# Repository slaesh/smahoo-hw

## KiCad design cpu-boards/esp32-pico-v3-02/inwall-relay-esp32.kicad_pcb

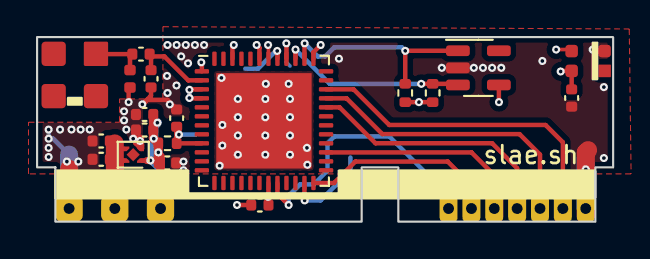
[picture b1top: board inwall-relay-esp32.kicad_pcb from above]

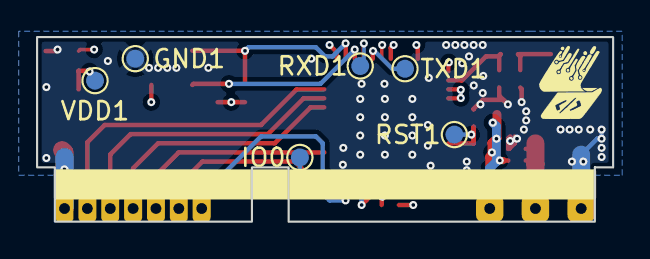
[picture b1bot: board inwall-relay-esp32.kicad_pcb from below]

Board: 4 copper layers, 32.0 x 10.3 mm, 26 parts (6 on the bottom side), 17 nets.

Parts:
C1, C2, C7: 1uF; C_0402_1005Metric
C3: 4.3nH; C_0402_1005Metric
C4: 0R; C_0402_1005Metric
C5: C; L_0402_1005Metric
C6, C8: 10uF; C_0402_1005Metric
C9, C10, C11: 100nF; C_0402_1005Metric
D1: WS2812B-2020; ws2812b-2020
GND1: TestPoint; TestPoint_Pad_D1.0mm
IO0: TestPoint; TestPoint_Pad_D1.0mm
J1: Conn_01x09_Male; inwall-relay-cpu
J2: ANTENNA; antenna_molex_479480001
R1, R2, R3: 10k; R_0402_1005Metric
RST1: TestPoint; TestPoint_Pad_D1.0mm
RXD1: TestPoint; TestPoint_Pad_D1.0mm
TXD1: TestPoint; TestPoint_Pad_D1.0mm
U1: ESP32-PICO-D4; QFN-48-1EP_7x7mm_P0.5mm_EP5.3x5.3mm
U2: NCP167; OnSemi_XDFN4-1EP_1.0x1.0mm_EP0.52x0.52mm
U3: 24AA02-OT; SOT-23-5
VDD1: TestPoint; TestPoint_Pad_D1.0mm

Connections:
BOARD_IO0: J1.4, U1.34 (IO5)
BOARD_IO1: J1.5, U1.33 (SD1)
BOARD_IO2: J1.6, U1.32 (SD0)
BOARD_IO4: J1.8, U1.24 (IO4)
BOARD_IO5: J1.9, U1.20 (IO13)
ESP_ANT: C3.1, C4.1, U1.2 (LNA_IN)
GND: C1.2, C2.2, C3.2, C5.1, C6.2, C7.2, C8.2, C9.2, C10.2, C11.2, D1.2 (VSS), GND1.1, J1.1, U1.49 (GND), U2.2 (GND), U3.2 (GND)
unnamed: C4.2, C5.2, J2.1
unnamed: C7.1, R1.2, RST1.1, U1.9 (EN)
unnamed: IO0.1, U1.23 (IO0)
unnamed: RXD1.1, U1.40 (U0RXD/IO3)
unnamed: TXD1.1, U1.41 (U0TXD/IO1)
SCL: R3.1, U1.38 (IO19), U3.1 (SCL)
SDA: R2.1, U1.39 (IO22), U3.3 (SDA)
VDD3V3: C2.1, C6.1, C9.1, C10.1, C11.1, D1.4 (VDD), J1.3, R1.1, R2.2, R3.2, U1.1 (VDDA), U1.3 (VDDA3P3), U1.4 (VDDA3P3), U1.19 (VDD3P3_RTC), U1.37 (VDD3P3_CPU), U1.43 (VDDA), U1.46 (VDDA), U2.1 (VOUT), U3.4 (VCC), VDD1.1
VIN: C1.1, C8.1, J1.2, U2.3 (/EN), U2.4 (VIN)
WS2812_DIN: D1.3 (DIN), U1.42 (IO21)

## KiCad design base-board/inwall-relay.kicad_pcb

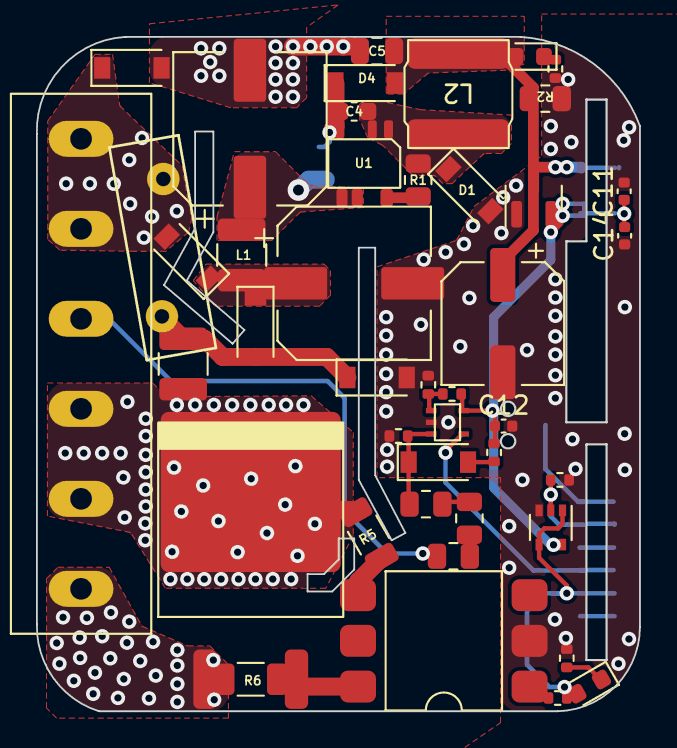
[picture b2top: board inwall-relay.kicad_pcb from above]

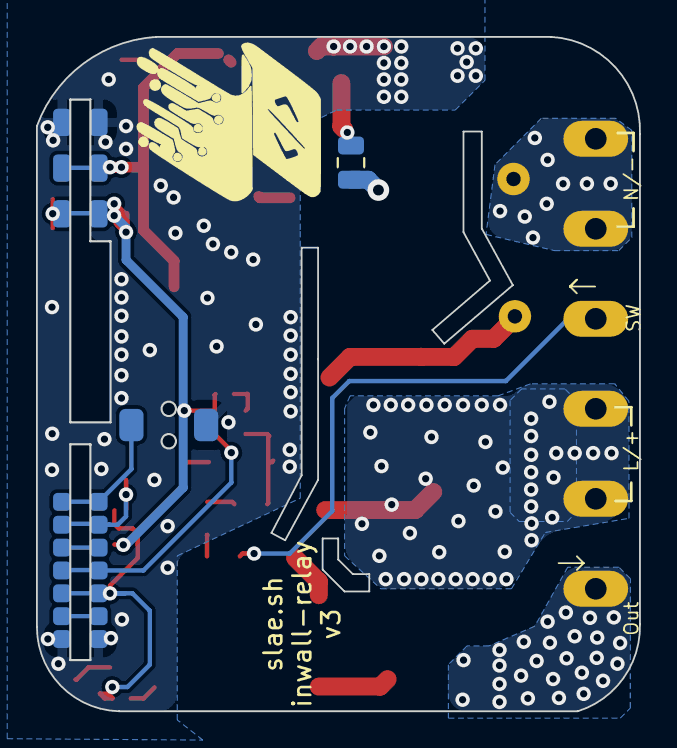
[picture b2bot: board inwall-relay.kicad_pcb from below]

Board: 2 copper layers, 33.5 x 37.5 mm, 46 parts (2 on the bottom side), 27 nets.

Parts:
C1, C3: 3.3uF; CP_Elec_8x10
C4: 1uF/16V; C_0603_1608Metric
C5: 22uF; C_0805_2012Metric
C8: 470uF; CP_Elec_6.3x7.7
C9: optional: 10pF / 500V; C_0805_2012Metric
C11: 22uF; C_0402_1005Metric
C12, C14: 100n; C_0402_1005Metric
D1: BAS21GWX; D_SOD-123
D2, D3, D4, D6, D7, D8: 1N4007; D_SOD-123
F1: Polyfuse; Fuse_1210_3225Metric
J1: IWR_CPU_MODULE; inwall-relay-cpu-female
J2: Conn_01x06_Female; WJ126-5.0
L1: 1mH; L_1210_3225Metric
L2: 470uH; L_6x6mm
LED1: blue; LED_0603_1608Metric
LED2: orange; LED_0603_1608Metric
Q1: BTA16-800B; D2PAK
R1: .3R; R_0805_2012Metric
R2: 1.5k; R_0805_2012Metric
R4, R20: 1.2k; R_0402_1005Metric
R5: 100R; R_1206_3216Metric
R6: 330R; R_1206_3216Metric
R10: 680R; R_0402_1005Metric
R11, R29, R30, R31, R32: 10k; R_0402_1005Metric
R26, R27, R28: 300k; R_0805_2012Metric
RV1: Varistor; RV_Disc_D12mm_W3.9mm_P7.5mm
SW1: SW_Push; TS-1088C-02526
U1: BP2525; sot33-5a
U2: MOC3063M; SMDIP-6_W9.53mm
U3: APE8865N-15-HF-3; SOT-23
U6: 74LVC1G80; SOT-353_SC-70-5
U7: TC75S56; SSOP-5-0.65

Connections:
/VIN_L_FUSED: D2.2 (A), D3.1 (K), F1.2, RV1.1
BOARD_IO1: J1.5, LED2.2 (A), R10.1, U6.1 (D), U6.4 (~Q)
BOARD_IO2: J1.6, U7.4
BOARD_IO4: J1.8, R11.2, U6.2 (C)
BOARD_IO5: J1.9, SW1.2
BP25xx_GND: C4.2, D1.1 (K), L2.1, R1.1, U1.1 (GND), U1.2 (SEL)
D: C3.1, C9.1, L1.2, U1.4 (DRAIN)
GND: C1.2, C3.2, C5.2, C8.2, C11.2, C12.2, C14.1, D1.2 (A), D3.2 (A), D7.2 (A), J1.1, R2.1, R4.2, R11.1, R20.2, R30.2, R32.2, SW1.1, U2.2, U3.1 (GND), U6.3 (GND), U7.2 (V-)
L_OUT: J2.6, Q1.1 (A1), R6.1
unnamed: C4.1, C9.2, D4.1 (K), U1.3 (VCC)
unnamed: D8.2 (A), R29.2
unnamed: D8.1 (K), R28.1, R30.1, U7.3 (-)
unnamed: LED1.1 (K), R4.1
unnamed: LED2.1 (K), R20.1
unnamed: R10.2, U2.1
unnamed: R26.1, R27.2
unnamed: R27.1, R28.2
unnamed: R1.2, U1.5 (CS)
unnamed: R31.2, R32.1, U7.1 (+)
TRIAC_EN1: Q1.3 (G), R6.2, U2.6
TRIAC_EN2: R5.1, U2.4
VDD3V3: C11.1, C12.1, C14.2, J1.3, R29.1, R31.1, U3.2 (VO), U6.5 (VCC), U7.5 (V+)
VDD5: C5.1, C8.1, D4.2 (A), J1.2, L2.2, LED1.2 (A), R2.2, U3.3 (VI)
VIN_L: F1.1, J2.4, J2.5, Q1.2 (A2), R5.2
VIN_L+: C1.1, D2.1 (K), D6.1 (K), L1.1
VIN_N: D6.2 (A), D7.1 (K), J2.1, J2.2, RV1.2
VIN_SWITCH: J2.3, R26.2

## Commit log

2023-01-14 add esp32 cpu board
